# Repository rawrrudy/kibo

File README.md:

# Kibo
Say hi to Kibo! Kibo is a desktop companion robot that recognizes human emotions and responds through movement, sounds and visual feedback! 

This project was created for [Horizons | Hack Club](https://horizons.hackclub.com)!

---

---

## What is Kibo?

So the primary idea behind Kibo is for it to be a desktop companion that emotionally connects to people (especially teenagers) and keeps a track of their moods and emotions and to sort of create a register of behavioral patterns. It is designed to understand human emotions and respond through sound and visual feedback.

It has a lot of sensors and a custom designed PCB that pieces together Kibo!

---

## AI Usage
I only used AI in some parts of the frontend to make it look more user friendly and to add the mechanism of log in streaks. The entire rest of the project was made by me!

---

## Schematic and PCB Images

<details>
<summary><b>1. PCB Images</b></summary>

<br>

<p align="center">
 Image of the PCB used in Kibo!
</p>

<br>

<p align="center">
 3D view of the PCB used in Kibo!
</p>

<br>
</details>

<details>
<summary><b>2. Schematic Images</b></summary>

<br>

<br>

<br>

<p align="center">
 Schematic diagram of Kibo!
</p>

<br>
</details>

---

## How to Build/Run?
> Note: At the time of writing, this is the first version/prototype of Kibo. After getting my project reviewed and accepted, I plan on adding much more features and the firmware will change based on those factors!

Please check the [BOM](BOM.csv) before building this project!

<details>

<summary><b> Hardware </b></summary> 

<br>

1. Fabricate the PCB using the [Gerber](hardware/gerbers) files provided.
2. Solder the ESP32-WROOM-32 and supporting components onto the PCB.
3. Solder the USB-C connector, CP2102N, transistors, resistors, capacitors, and other components according to the PCB schematic.
4. Connect Kibo's external electronic components to their designated connections according to the final wiring diagram.
5. Mount the PCB and electronics inside the Kibo enclosure.
6. Position the speaker flat underneath the top lid, aligned with the integrated speaker grille.
7. Route all necessary wires through the enclosure openings and secure the components.
8. Close the enclosure and verify that no wires or components interfere with the lid.

</details>

<details>
<summary><b> Firmware Installation </b></summary> 
  
<br>

1. Install [Arduino IDE](https://www.arduino.cc/en/software/)
2. Install ESP32 board support through the Arduino IDE Board Manager.
3. Connect Kibo to your computer using the USB-C port.
4. Select the appropriate ESP32 board in Arduino IDE.
5. Select the COM port corresponding to Kibo's CP2102N USB interface.
6. Open the [firmware](hardware/firmware/kibo_v1.ino) files.
7. Compile the firmware to verify that there are no errors.
8. Upload the firmware to the ESP32.
9. Open the Serial Monitor at 115200 baud.
10. Confirm that Kibo prints its startup information and reports that the system is ready.

</details>

<details>
<summary><b> Wiring </b></summary> 
  
<br>

Connect all the electronic components of Kibo according to the schematic.

| Component | Connection / Function |
|------------|----------------|
| ESP32 WROOM 32 | Main controller |
| CP2102N | USB to UART communication|
| USB-C | Power + programming |
| SS8050 ×2 | Automatic boot |
| RESET button | ESP32 reset |
| BOOT button | ESP32 bootloader mode |
| Speaker | Audio Output |
| Sensors/peripherals | Connected according to the final Kibo wiring|

Refer to the PCB schematic and hardware documentation in the [hardware](hardware) directory for detailed connections and pin assignments.

</details>

<details> 
<summary><b> Backend Setup </b></summary>
  
<br>

1. Navigate to the backend directory.
```bash
cd backend
```

2. Create and activate a Python virtual environment.
```bash
python -m venv venv
```

3. Activate the virtual environment:
- Windows:
```bash
venv\Scripts\activate
```
- Linux / macOS:
```bash
source venv/bin/activate
```

4. Install dependencies.
```bash
pip install -r requirements.txt
```
5. Start the backend server using the project's configured entry point.
```bash
uvicorn app.main:app --reload
```
</details>

<details> 
<summary><b> Frontend Setup </b></summary> 
  
<br>

1. Navigate to the frontend directory.
```bash
cd frontend
```
2. Install dependencies.
```bash
npm install
```
3. Start the development server.
```bash
npm run dev
```
6. Open the URL displayed in the terminal.
7. Ensure the backend server is running and connected to the database.
8. Verify that the Kibo interface loads correctly.

</details>

<details>
<summary><b> Operation </b></summary>
  
<br>

1. Power on Kibo through USB-C.
2. Wait for the ESP32 to complete its startup sequence.
3. Open the Serial Monitor at 115200 baud.
4. Type:
```bash
help
```
5. Test the available commands:
```bash
status
info
version
```
6. Test Wi Fi discovery:
```bash
wifi scan
```
7. Verify that the ESP32 reports a successful connection and provides an IP address.
8. Verify communication between the hardware and software components.
9. Voila! Your very own version of the Kibo is ready!

</details>

---

## Images

<table>
  <tr>
    <td align="center">
      
    </td>
    <td align="center">
      
    </td>
  </tr>
  <tr>
    <td align="center">
      
    </td>
    <td align="center">
      
    </td>
  </tr>
  <tr>
    <td align="center">
      
    </td>
    <td align="center">
      
    </td>
  </tr>
</table>

## Acknowledgements
I would like to thank-

[KiCad](https://www.kicad.org/)

[Arduino](https://www.arduino.cc/)

and the entire team at [Horizons | Hack Club](https://horizons.hackclub.com) to conduct such an awesome experience!

## License 

This project is licensed under the MIT License. See the [LICENSE](LICENSE) file for more details.

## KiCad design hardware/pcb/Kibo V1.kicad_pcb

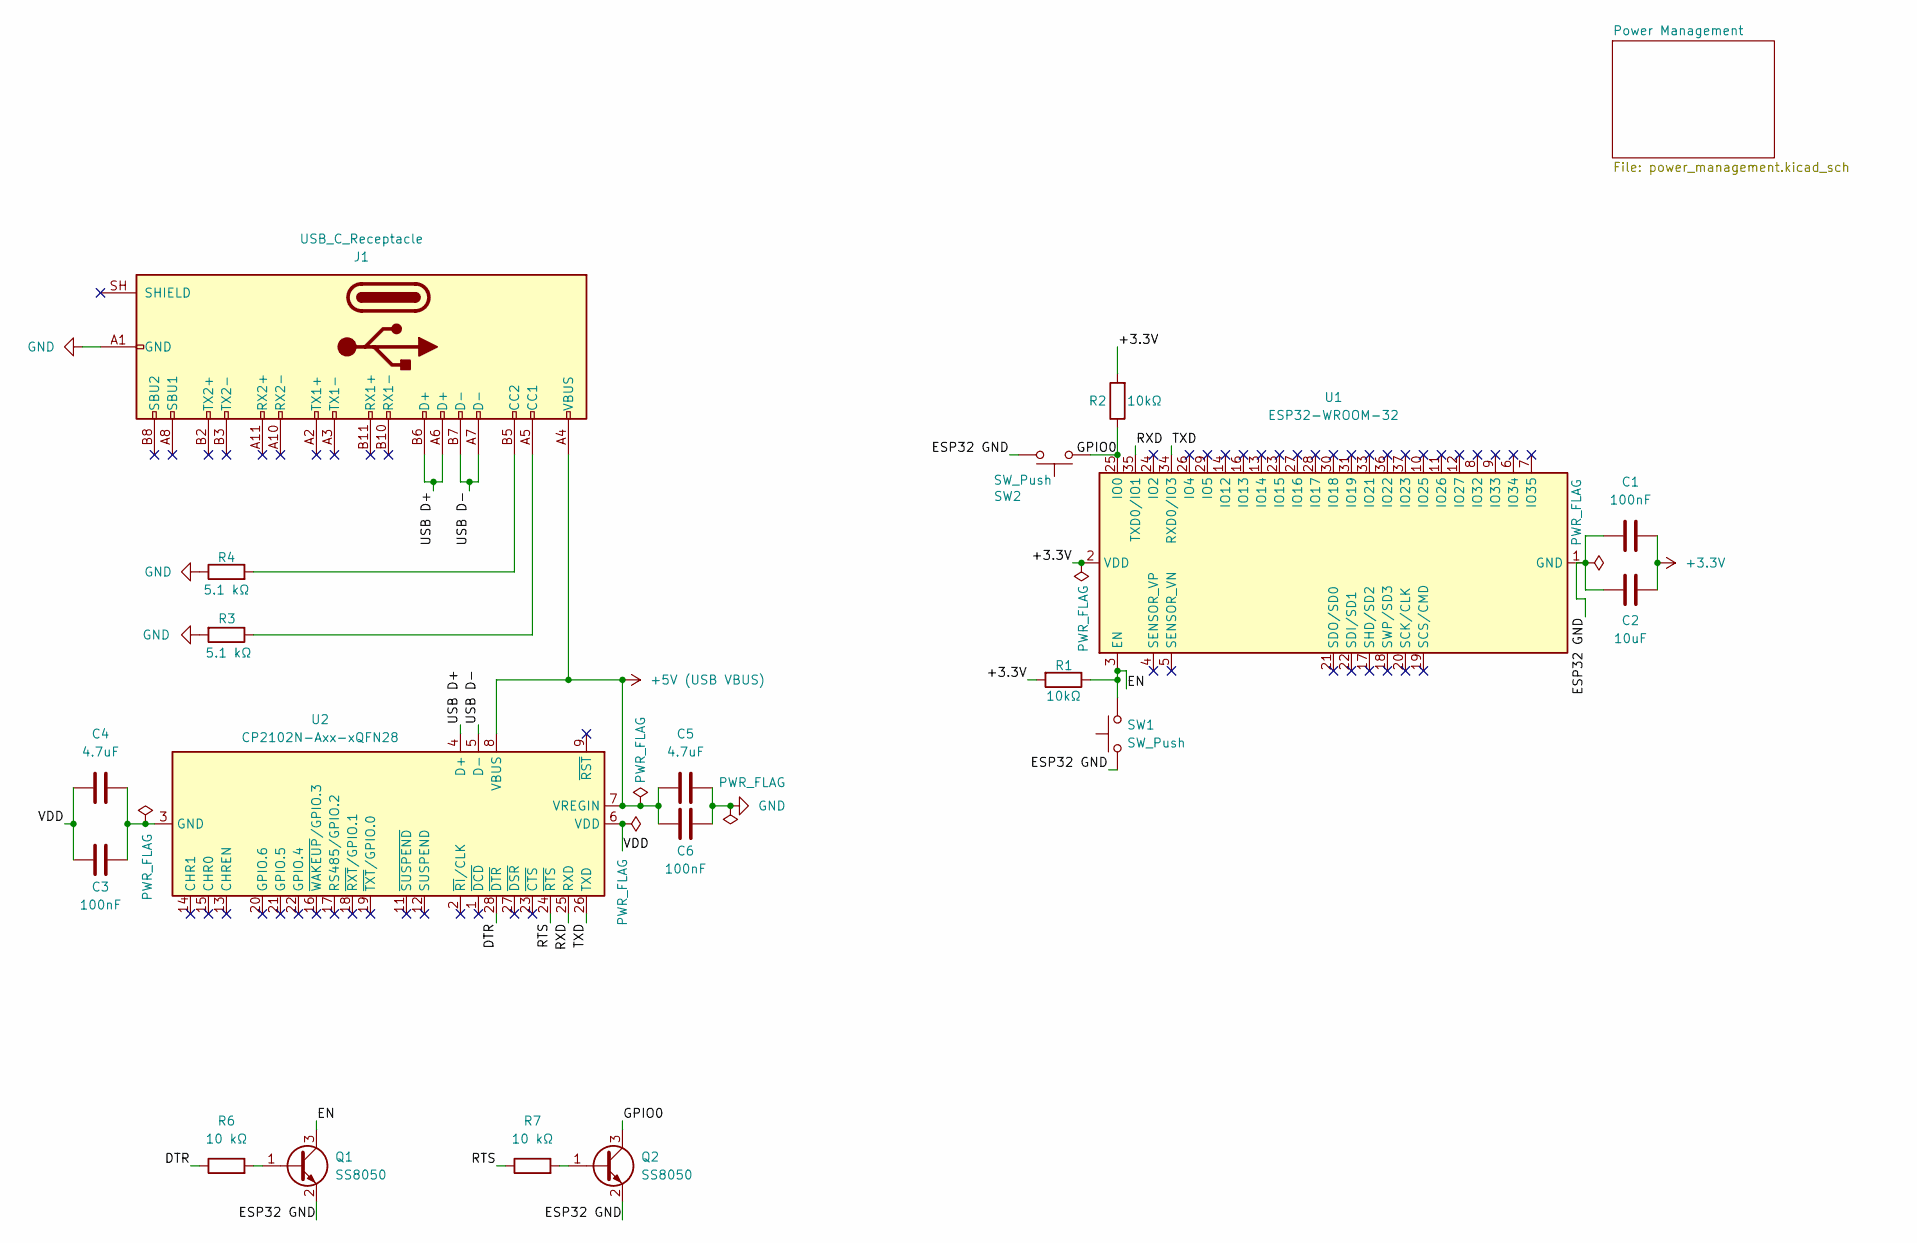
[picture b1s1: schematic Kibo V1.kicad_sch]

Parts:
C1, C3, C6: 100nF; C_0603_1608Metric
C2: 10uF; C_0603_1608Metric
C4, C5: 4.7uF; C_0603_1608Metric
J1: USB_C_Receptacle; USB_C_Receptacle_Amphenol_12401548E4-2A
Q1, Q2: SS8050; SOT-23
R1, R2: 10kΩ; R_0603_1608Metric
R3, R4: 5.1 kΩ; R_0603_1608Metric
R6, R7: 10 kΩ; R_0603_1608Metric
SW1, SW2: SW_Push; SW_SPST_TL3342
U1: ESP32-WROOM-32
U2: CP2102N-Axx-xQFN28; QFN-28-1EP_5x5mm_P0.5mm_EP3.35x3.35mm

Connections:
+3.3V: C1.2, C2.2, R1.2, R2.2, U1.2 (VDD)
+5V (USB VBUS): C5.1, C6.1, J1.A4 (VBUS), J1.A9 (VBUS), J1.B4 (VBUS), J1.B9 (VBUS), U2.7 (VREGIN), U2.8 (VBUS)
/DTR: R6.1, U2.28 (~DTR)
/EN: Q1.3 (C), R1.1, SW1.2, U1.3 (EN)
/ESP32 GND: C1.1, C2.1, Q1.2 (E), Q2.2 (E), SW1.1, SW2.2, U1.1 (GND), U1.15 (GND), U1.38 (GND), U1.39 (GND)
/GPIO0: Q2.3 (C), R2.1, SW2.1, U1.25 (IO0)
/RTS: R7.1, U2.24 (~RTS)
/RXD: U1.35 (TXD0/IO1), U2.25 (RXD)
/TXD: U1.34 (RXD0/IO3), U2.26 (TXD)
/USB D+: J1.A6 (D+), J1.B6 (D+), U2.4 (D+)
/USB D-: J1.A7 (D-), J1.B7 (D-), U2.5 (D-)
/VDD: C3.1, C4.1, U2.6 (VDD)
GND: C5.2, C6.2, J1.A1 (GND), J1.A12 (GND), J1.B1 (GND), J1.B12 (GND), R3.2, R4.1
unnamed: C3.2, C4.2, U2.3 (GND), U2.29 (GND)
unnamed: J1.A5 (CC1), R3.1
unnamed: J1.B5 (CC2), R4.2
unnamed: Q1.1 (B), R6.2
unnamed: Q2.1 (B), R7.2

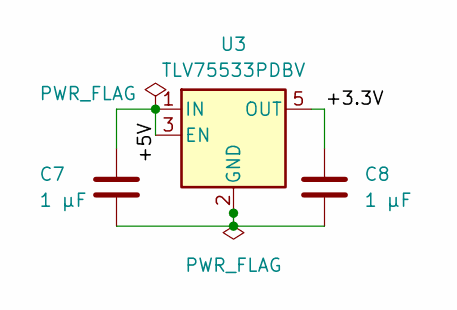
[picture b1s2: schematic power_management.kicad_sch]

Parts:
C7, C8: 1 µF; C_0603_1608Metric
U3: TLV75533PDBV; SOT-23-5

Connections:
/Power Management/+3.3V: C8.1, U3.5 (OUT)
/Power Management/+5V: C7.2, U3.1 (IN), U3.3 (EN)
unnamed: C7.1, C8.2, U3.2 (GND)

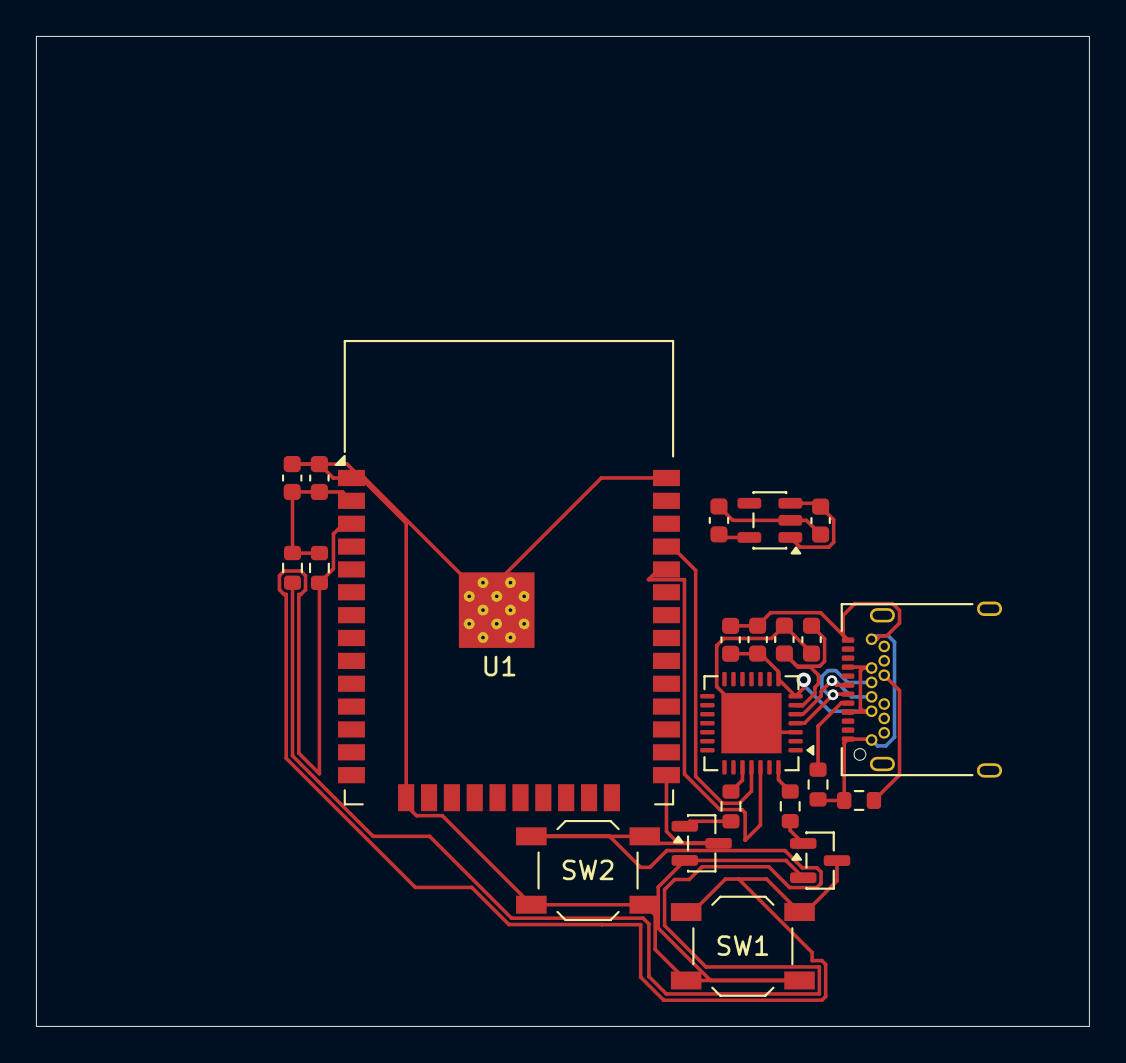
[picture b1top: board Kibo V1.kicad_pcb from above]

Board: 2 copper layers, 58.5 x 55.0 mm, 22 parts (0 on the bottom side), 21 nets.

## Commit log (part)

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2026-06-21 Create journal images
2026-06-27 Initial Kibo project
